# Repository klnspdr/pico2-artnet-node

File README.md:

# pico2-artnet-node

## Upload to JLCPCB
To generate files for uploading to JLCPCB, the plugin ["Fabrication Toolkit"](https://github.com/bennymeg/Fabrication-Toolkit) is used. It generates Gerber and BOM/Pick'n'Places files. Upload the `.zip` in `production/` as the Gerber file and in PCBA upload `bom.csv`  and `positions.csv`

## Estimated Price

PCB + SMD Components: 8.146$ / board
Missing Components:
    - 4x XLR Connectors (~1.40€ / piece)
    - 1x WizNet W5500-EVB-PICO2 (~12€ / piece)
    - 1x B0505S (~1.05$ / piece)
    - 1x WIZPoE Module (~8€ / piece)
    - 2x 1x20 2.54mm Pinsocket THT Vertical (~0.15$ / piece)
    - 3x 1x4 2.54mm Pinsocket THT Vertical (~0.05$ / piece)

=> Overall cost per board (without shipping): ~20€ / ~28€ (without/with PoE)

## Possible other features / TODOs
- [x] LED showing powered state
- [x] Pinheader for I2C
- [x] Levelshifter for WS2812 etc driving (maybe with separate power input?)
- [ ] Test points
- [x] Silkscreen
- [ ] Mounting Holes
- [ ] JLC Ordering Number / mounting holes for PCBA

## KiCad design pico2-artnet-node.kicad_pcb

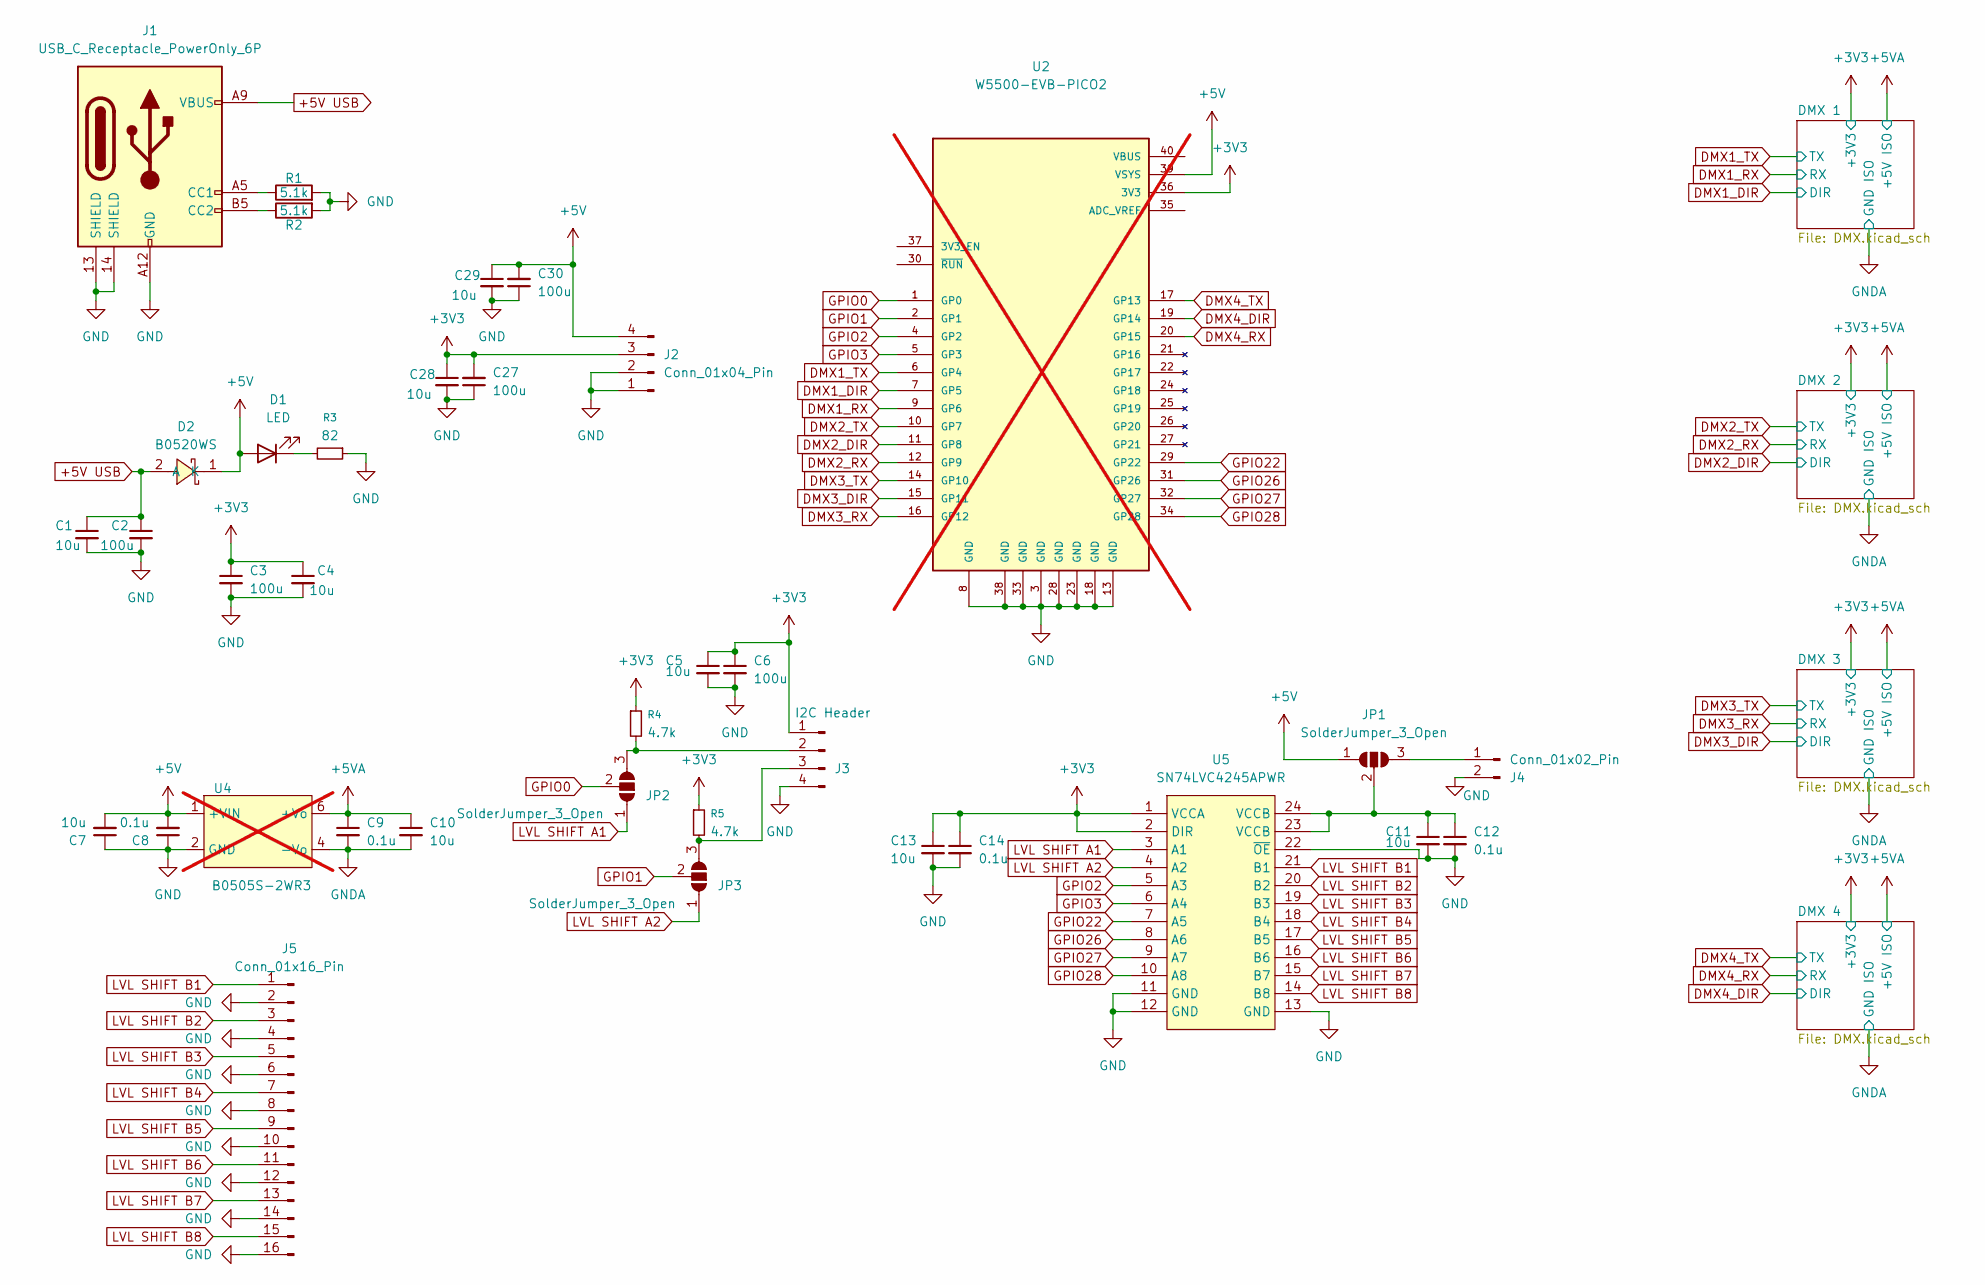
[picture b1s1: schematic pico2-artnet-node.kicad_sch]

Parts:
C1, C4, C5, C7, C10, C11, C13, C28, C29: 10u; C_0603_1608Metric; LCSC Part C19702
C2, C3, C6, C27, C30: 100u; C_1206_3216Metric; LCSC Part C15008
C8, C9, C12, C14: 0.1u; C_0603_1608Metric; LCSC Part C14663
D1: LED; LED_0805_2012Metric; LCSC Part C2297
D2: B0520WS; SOD-323_L1.7-W1.3-LS2.6-RD-1; LCSC Part C7502696
J1: USB_C_Receptacle_PowerOnly_6P; USB-C-SMD_YPE-C-6PWTL-10-0108_Board-overhang; LCSC Part C30167331
J2: Conn_01x04_Pin; FanPinHeader_1x04_P2.54mm_Vertical
J3: I2C Header; FanPinHeader_1x04_P2.54mm_Vertical
J4: Conn_01x02_Pin; PinSocket_1x02_P2.54mm_Vertical
J5: Conn_01x16_Pin; PinSocket_1x16_P2.54mm_Vertical
JP1, JP2, JP3: SolderJumper_3_Open; PinHeader_1x03_P2.54mm_Vertical
R1, R2: 5.1k; R_0603_1608Metric
R3: 82; R_0603_1608Metric
R4, R5: 4.7k; R_0603_1608Metric
U2: W5500-EVB-PICO2; MODULE_W5500-EVB-PICO2; PARTREV 2022-01-28; not fitted
U4: B0505S-2WR3; PWRM-TH_BXXXXS-2WR3; LCSC Part C5369473; not fitted
U5: SN74LVC4245APWR; TSSOP-24_L7.8-W4.4-P0.65-LS6.4-BL; LCSC Part C7859

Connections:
+3V3: C3.1, C4.1, C5.1, C6.1, C13.1, C14.1, C27.2, C28.1, J2.3, J3.1, R4.1, R5.1, U2.36 (3V3), U5.1 (VCCA), U5.2 (DIR); also elsewhere on the board
+5V: C7.2, C8.2, C29.1, C30.2, D1.2 (A), D2.1 (K), J2.4, JP1.1 (A), U2.39 (VSYS), U4.1 (+VIN)
+5V USB: C1.1, C2.1, D2.2 (A), J1.A9 (VBUS), J1.B9 (VBUS)
+5VA: C9.1, C10.1, U4.6 (+Vo); also elsewhere on the board
DMX1_DIR: U2.7 (GP5); also elsewhere on the board
DMX1_RX: U2.9 (GP6); also elsewhere on the board
DMX1_TX: U2.6 (GP4); also elsewhere on the board
DMX2_DIR: U2.11 (GP8); also elsewhere on the board
DMX2_RX: U2.12 (GP9); also elsewhere on the board
DMX2_TX: U2.10 (GP7); also elsewhere on the board
DMX3_DIR: U2.15 (GP11); also elsewhere on the board
DMX3_RX: U2.16 (GP12); also elsewhere on the board
DMX3_TX: U2.14 (GP10); also elsewhere on the board
DMX4_DIR: U2.19 (GP14); also elsewhere on the board
DMX4_RX: U2.20 (GP15); also elsewhere on the board
DMX4_TX: U2.17 (GP13); also elsewhere on the board
GND: C1.2, C2.2, C3.2, C4.2, C5.2, C6.2, C7.1, C8.1, C11.2, C12.2, C13.2, C14.2, C27.1, C28.2, C29.2, C30.1, J1.13 (SHIELD), J1.14 (SHIELD), J1.A12 (GND), J1.B12 (GND), J2.1, J2.2, J3.4, J4.2, J5.2, J5.4, J5.6, J5.8, J5.10, J5.12, J5.14, J5.16, R1.2, R2.2, R3.1, U2.3 (GND), U2.8 (GND), U2.13 (GND), U2.18 (GND), U2.23 (GND), U2.28 (GND), U2.33 (GND), U2.38 (GND), U4.2 (GND), U5.11 (GND), U5.12 (GND), U5.13 (GND), U5.22 (~OE); also elsewhere on the board
GNDA: C9.2, C10.2, U4.4 (-Vo); also elsewhere on the board
GPIO0: JP2.2 (C), U2.1 (GP0)
GPIO1: JP3.2 (C), U2.2 (GP1)
GPIO2: U2.4 (GP2), U5.5 (A3)
GPIO3: U2.5 (GP3), U5.6 (A4)
GPIO22: U2.29 (GP22), U5.7 (A5)
GPIO26: U2.31 (GP26), U5.8 (A6)
GPIO27: U2.32 (GP27), U5.9 (A7)
GPIO28: U2.34 (GP28), U5.10 (A8)
LVL SHIFT A1: JP2.1 (A), U5.3 (A1)
LVL SHIFT A2: JP3.1 (A), U5.4 (A2)
LVL SHIFT B1: J5.1, U5.21 (B1)
LVL SHIFT B2: J5.3, U5.20 (B2)
LVL SHIFT B3: J5.5, U5.19 (B3)
LVL SHIFT B4: J5.7, U5.18 (B4)
LVL SHIFT B5: J5.9, U5.17 (B5)
LVL SHIFT B6: J5.11, U5.16 (B6)
LVL SHIFT B7: J5.13, U5.15 (B7)
LVL SHIFT B8: J5.15, U5.14 (B8)
unnamed: D1.1 (K), R3.2
unnamed: J1.A5 (CC1), R1.1
unnamed: J1.B5 (CC2), R2.1
unnamed: J3.2, JP2.3 (B), R4.2
unnamed: J3.3, JP3.3 (B), R5.2
unnamed: J4.1, JP1.3 (B)
unnamed: C11.1, C12.1, JP1.2 (C), U5.23 (VCCB), U5.24 (VCCB)

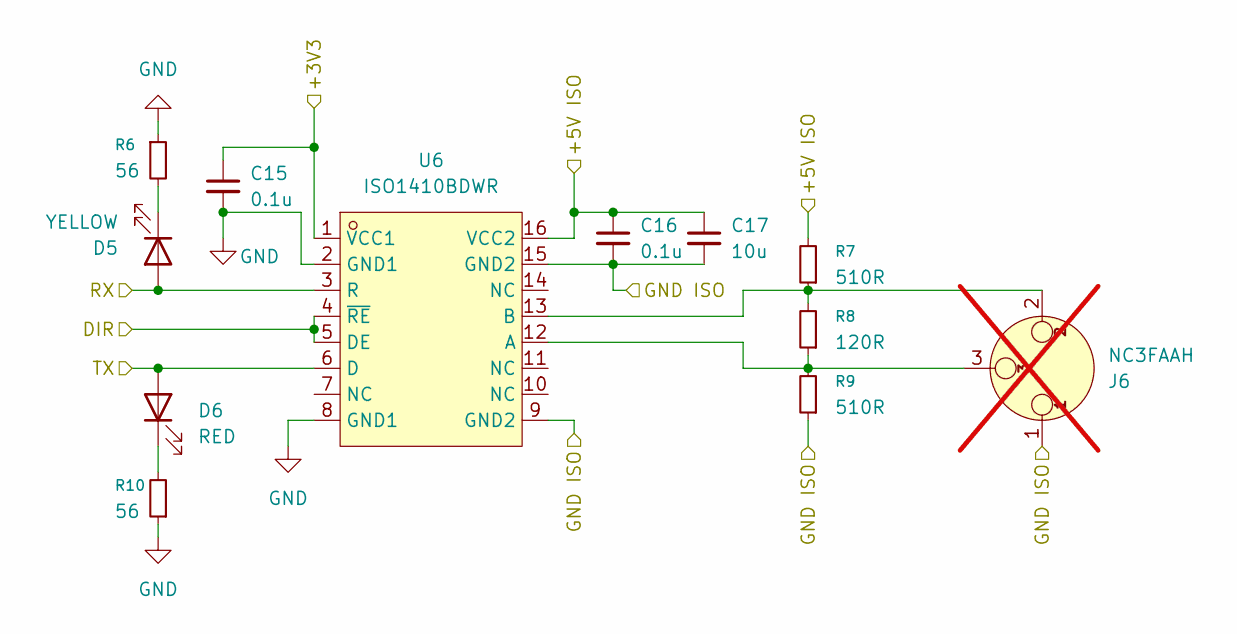
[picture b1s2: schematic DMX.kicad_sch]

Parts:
C15, C16: 0.1u; C_0603_1608Metric; LCSC Part C14663
C17: 10u; C_0603_1608Metric; LCSC Part C19702
D5: YELLOW; LED_0805_2012Metric; LCSC Part C2296
D6: RED; LED_0805_2012Metric; LCSC Part C84256
J6: NC3FAAH; Jack_XLR_Neutrik_NC3FAAH_Horizontal_Board-Overhang; LCSC Part C368521; not fitted
R6, R10: 56; R_0603_1608Metric
R7, R9: 510R; R_0603_1608Metric
R8: 120R; R_0603_1608Metric
U6: ISO1410BDWR; SOIC-16_L10.3-W7.5-P1.27-LS10.3-BL; LCSC Part C2671027

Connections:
+3V3: C15.1, U6.1 (VCC1); also elsewhere on the board
+5VA: C16.1, C17.1, R7.2, U6.16 (VCC2); also elsewhere on the board
DMX1_DIR: U6.4 (~RE), U6.5 (DE); also elsewhere on the board
DMX1_RX: D5.2 (A), U6.3 (R); also elsewhere on the board
DMX1_TX: D6.2 (A), U6.6 (D); also elsewhere on the board
GND: C15.2, R6.1, R10.1, U6.2 (GND1), U6.8 (GND1); also elsewhere on the board
GNDA: C16.2, C17.2, J6.1, R9.1, U6.9 (GND2), U6.15 (GND2); also elsewhere on the board
unnamed: D5.1 (K), R6.2
unnamed: D6.1 (K), R10.2
unnamed: J6.3, R8.1, R9.2, U6.12 (A)
unnamed: J6.2, R7.1, R8.2, U6.13 (B)

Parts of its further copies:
C18, C19, C21, C22, C24, C25: 0.1u; C_0603_1608Metric; LCSC Part C14663
C20, C23, C26: 10u; C_0603_1608Metric; LCSC Part C19702
D7, D9, D11: YELLOW; LED_0805_2012Metric; LCSC Part C2296
D8, D10, D12: RED; LED_0805_2012Metric; LCSC Part C84256
J7, J8, J9: NC3FAAH; Jack_XLR_Neutrik_NC3FAAH_Horizontal_Board-Overhang; LCSC Part C368521; not fitted
R11, R15, R16, R20, R21, R25: 56; R_0603_1608Metric
R12, R14, R17, R19, R22, R24: 510R; R_0603_1608Metric
R13, R18, R23: 120R; R_0603_1608Metric
U7, U8, U9: ISO1410BDWR; SOIC-16_L10.3-W7.5-P1.27-LS10.3-BL; LCSC Part C2671027

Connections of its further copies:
+3V3: C18.1, C21.1, C24.1, U7.1 (VCC1), U8.1 (VCC1), U9.1 (VCC1); also elsewhere on the board
+5VA: C19.1, C20.1, C22.1, C23.1, C25.1, C26.1, R12.2, R17.2, R22.2, U7.16 (VCC2), U8.16 (VCC2), U9.16 (VCC2); also elsewhere on the board
DMX2_DIR: U7.4 (~RE), U7.5 (DE); also elsewhere on the board
DMX2_RX: D7.2 (A), U7.3 (R); also elsewhere on the board
DMX2_TX: D8.2 (A), U7.6 (D); also elsewhere on the board
DMX3_DIR: U8.4 (~RE), U8.5 (DE); also elsewhere on the board
DMX3_RX: D9.2 (A), U8.3 (R); also elsewhere on the board
DMX3_TX: D10.2 (A), U8.6 (D); also elsewhere on the board
DMX4_DIR: U9.4 (~RE), U9.5 (DE); also elsewhere on the board
DMX4_RX: D11.2 (A), U9.3 (R); also elsewhere on the board
DMX4_TX: D12.2 (A), U9.6 (D); also elsewhere on the board
GND: C18.2, C21.2, C24.2, R11.1, R15.1, R16.1, R20.1, R21.1, R25.1, U7.2 (GND1), U7.8 (GND1), U8.2 (GND1), U8.8 (GND1), U9.2 (GND1), U9.8 (GND1); also elsewhere on the board
GNDA: C19.2, C20.2, C22.2, C23.2, C25.2, C26.2, J7.1, J8.1, J9.1, R14.1, R19.1, R24.1, U7.9 (GND2), U7.15 (GND2), U8.9 (GND2), U8.15 (GND2), U9.9 (GND2), U9.15 (GND2); also elsewhere on the board
unnamed: D7.1 (K), R11.2
unnamed: D8.1 (K), R15.2
unnamed: D9.1 (K), R16.2
unnamed: D10.1 (K), R20.2
unnamed: D11.1 (K), R21.2
unnamed: D12.1 (K), R25.2
unnamed: J7.3, R13.1, R14.2, U7.12 (A)
unnamed: J7.2, R12.1, R13.2, U7.13 (B)
unnamed: J8.3, R18.1, R19.2, U8.12 (A)
unnamed: J8.2, R17.1, R18.2, U8.13 (B)
unnamed: J9.3, R23.1, R24.2, U9.12 (A)
unnamed: J9.2, R22.1, R23.2, U9.13 (B)

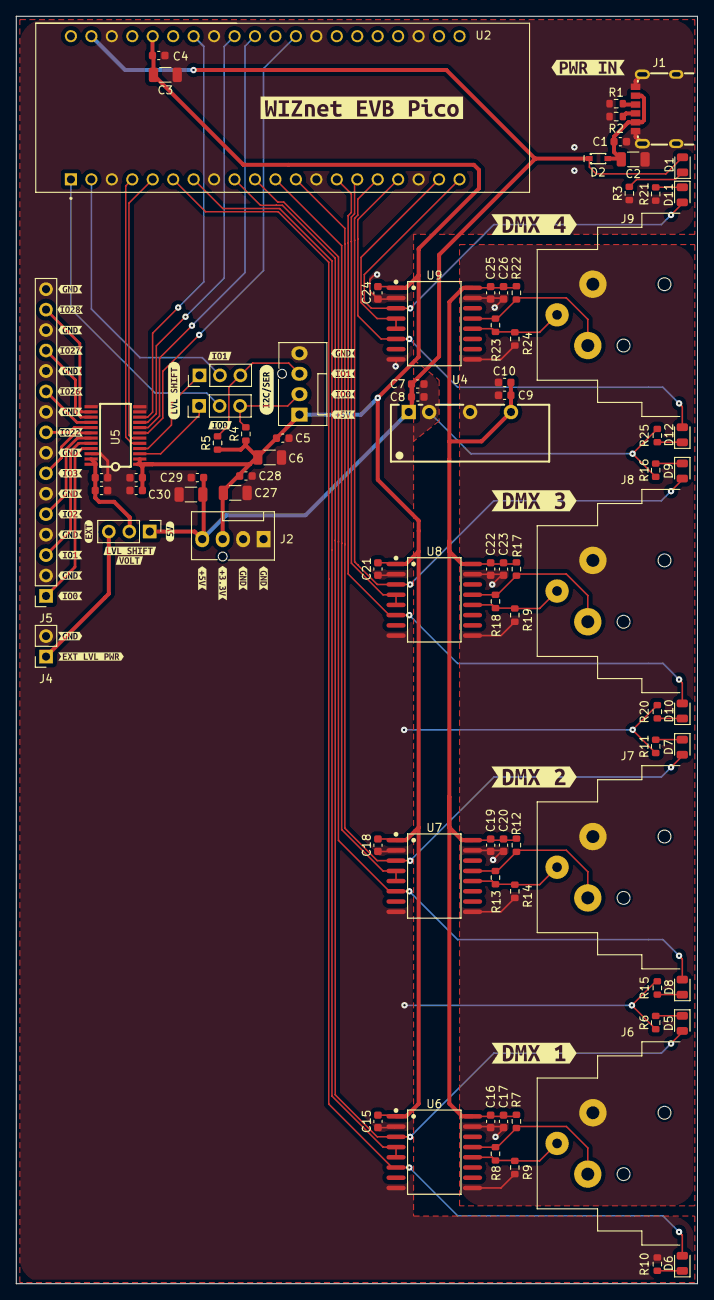
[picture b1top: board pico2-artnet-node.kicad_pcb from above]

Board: 2 copper layers, 84.6 x 157.4 mm, 124 parts (0 on the bottom side), 59 nets.

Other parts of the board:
kibuzzard-68DD1E8E: G***; kibuzzard-68DD1E8E
kibuzzard-68DD1E9C: G***; kibuzzard-68DD1E9C
kibuzzard-68DD1EFE: G***; kibuzzard-68DD1EFE
kibuzzard-68DD1F08: G***; kibuzzard-68DD1F08
kibuzzard-68DD1F80: G***; kibuzzard-68DD1F80
kibuzzard-68DD3F78: G***; kibuzzard-68DD3F78
kibuzzard-68DD21E1, kibuzzard-68DD21E1#2, kibuzzard-68DD21E1#3, kibuzzard-68DD21E1#4, kibuzzard-68DD21E1#5, kibuzzard-68DD21E1#6, kibuzzard-68DD21E1#7, kibuzzard-68DD21E1#8: G***; kibuzzard-68DD21E1
kibuzzard-68DD22C2: G***; kibuzzard-68DD22C2
kibuzzard-68DD22D5: G***; kibuzzard-68DD22D5
kibuzzard-68DD22E0: G***; kibuzzard-68DD22E0
kibuzzard-68DD22E9: G***; kibuzzard-68DD22E9
kibuzzard-68DD22F0: G***; kibuzzard-68DD22F0
kibuzzard-68DD23A7: G***; kibuzzard-68DD23A7
kibuzzard-68DD23B6: G***; kibuzzard-68DD23B6
kibuzzard-68DD28CA: G***; kibuzzard-68DD28CA
kibuzzard-68DD43ED, kibuzzard-68DD43ED#2: G***; kibuzzard-68DD43ED
kibuzzard-68DD227C: G***; kibuzzard-68DD227C
kibuzzard-68DD228E: G***; kibuzzard-68DD228E
kibuzzard-68DD244B: G***; kibuzzard-68DD244B
kibuzzard-68DD245B: G***; kibuzzard-68DD245B
kibuzzard-68DD444E: G***; kibuzzard-68DD444E
kibuzzard-68DD501A: G***; kibuzzard-68DD501A
kibuzzard-68DD2296: G***; kibuzzard-68DD2296
kibuzzard-68DD2361: G***; kibuzzard-68DD2361
kibuzzard-68DD2414: G***; kibuzzard-68DD2414
kibuzzard-68DD2461: G***; kibuzzard-68DD2461
kibuzzard-68DD2906: G***; kibuzzard-68DD2906
kibuzzard-68DD2926: G***; kibuzzard-68DD2926
kibuzzard-68DD4448: G***; kibuzzard-68DD4448
kibuzzard-68DD4454, kibuzzard-68DD4454#2: G***; kibuzzard-68DD4454
kibuzzard-68DD5009: G***; kibuzzard-68DD5009

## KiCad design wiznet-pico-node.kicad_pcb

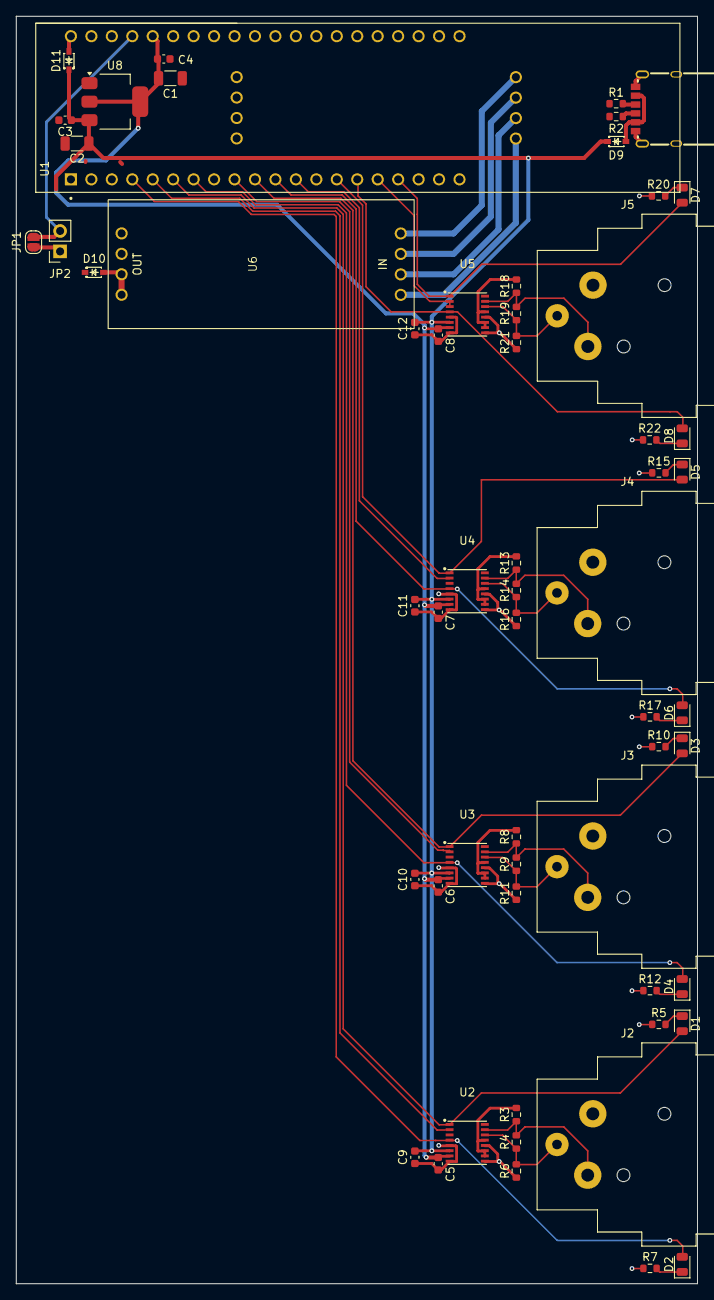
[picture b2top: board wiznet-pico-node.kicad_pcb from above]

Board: 2 copper layers, 84.6 x 157.4 mm, 59 parts (0 on the bottom side), 43 nets.

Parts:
C1, C2: 100u; C_1206_3216Metric
C3, C4, C5, C6, C7, C8, C9, C10, C11, C12: 10u; C_0603_1608Metric
D1, D3, D5, D7: YELLOW; LED_0805_2012Metric
D2, D4, D6, D8: RED; LED_0805_2012Metric
D9, D10, D11: B0520WS; SOD-323_L1.7-W1.3-LS2.6-RD-1
J2, J3, J4, J5: NC3FAAH; Jack_XLR_Neutrik_NC3FAAH_Horizontal
J6: USB_C_Receptacle_PowerOnly_6P; USB-C-SMD_YPE-C-6PWTL-10-0108
JP1: disable onboard LDO; SolderJumper-2_P1.3mm_Open_RoundedPad1.0x1.5mm
JP2: disable onboard LDO; PinSocket_1x02_P2.54mm_Vertical
R1, R2: 5.1k; R_0603_1608Metric
R3, R6, R8, R11, R13, R16, R18, R21: 510R; R_0603_1608Metric
R4, R9, R14, R19: 120R; R_0603_1608Metric
R5, R10, R15, R20: 75R; R_0603_1608Metric
R7, R12, R17, R22: 51R; R_0603_1608Metric
U1: W5500-EVB-PICO2; MODULE_W5500-EVB-PICO2
U2, U3, U4, U5: CA-IS2092A; LGA-16_L5.2-W4.7-P0.65-TL_CA-IS2062A-FRANK2
U6: WIZPoE Hat
U8: AMS1117-3.3; SOT-223-3_TabPin2

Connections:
+3V3: C1.1, C4.1, C5.1, C6.1, C7.1, C8.1, U1.36 (3V3), U2.7 (VDDL), U3.7 (VDDL), U4.7 (VDDL), U5.7 (VDDL), U8.2 (VO)
+5V: C2.1, C3.1, C9.1, C10.1, C11.1, C12.1, D9.1 (K), D10.1 (K), D11.1 (K), U2.6 (VDDP), U3.6 (VDDP), U4.6 (VDDP), U5.6 (VDDP), U8.3 (VI)
+5V PoE: D10.2 (A), U6.1 (5V)
+5V RP: D11.2 (A), U1.40 (VBUS)
+5V USB: D9.2 (A), J6.A9 (VBUS), J6.B9 (VBUS)
+5VA: R3.2, R8.2, R13.2, R18.2, U2.10 (VISOIN), U2.11 (VISOOUT), U2.13 (SEL), U3.10 (VISOIN), U3.11 (VISOOUT), U3.13 (SEL), U4.10 (VISOIN), U4.11 (VISOOUT), U4.13 (SEL), U5.10 (VISOIN), U5.11 (VISOOUT), U5.13 (SEL)
AGND: J2.1, J3.1, J4.1, J5.1, R6.1, R11.1, R16.1, R21.1, U2.9 (GND2), U2.12 (GND2), U3.9 (GND2), U3.12 (GND2), U4.9 (GND2), U4.12 (GND2), U5.9 (GND2), U5.12 (GND2)
DMX1_DIR: U1.5 (GP3), U2.2 (~RE), U2.3 (DE)
DMX1_RX: D1.2 (A), U1.6 (GP4), U2.1 (RO)
DMX1_TX: D2.2 (A), U1.4 (GP2), U2.4 (DI)
DMX2_DIR: U1.9 (GP6), U3.2 (~RE), U3.3 (DE)
DMX2_RX: D3.2 (A), U1.10 (GP7), U3.1 (RO)
DMX2_TX: D4.2 (A), U1.7 (GP5), U3.4 (DI)
DMX3_DIR: U1.12 (GP9), U4.2 (~RE), U4.3 (DE)
DMX3_RX: D5.2 (A), U1.14 (GP10), U4.1 (RO)
DMX3_TX: D6.2 (A), U1.11 (GP8), U4.4 (DI)
DMX4_DIR: U1.16 (GP12), U5.2 (~RE), U5.3 (DE)
DMX4_RX: D7.2 (A), U1.17 (GP13), U5.1 (RO)
DMX4_TX: D8.2 (A), U1.15 (GP11), U5.4 (DI)
GND: C1.2, C2.2, C3.2, C4.2, C5.2, C6.2, C7.2, C8.2, C9.2, C10.2, C11.2, C12.2, J6.13 (SHIELD), J6.14 (SHIELD), J6.A12 (GND), J6.B12 (GND), JP1.1 (A), JP2.1 (A), R1.2, R2.2, R5.1, R7.1, R10.1, R12.1, R15.1, R17.1, R20.1, R22.1, U1.3 (GND), U1.8 (GND), U1.13 (GND), U1.18 (GND), U1.23 (GND), U1.28 (GND), U1.33 (GND), U1.38 (GND), U1.42 (GND), U2.5 (GND1), U2.8 (GND1), U3.5 (GND1), U3.8 (GND1), U4.5 (GND1), U4.8 (GND1), U5.5 (GND1), U5.8 (GND1), U6.2 (GND), U8.1 (GND)
unnamed: D1.1 (K), R5.2
unnamed: D2.1 (K), R7.2
unnamed: D3.1 (K), R10.2
unnamed: D4.1 (K), R12.2
unnamed: D5.1 (K), R15.2
unnamed: D6.1 (K), R17.2
unnamed: D7.1 (K), R20.2
unnamed: D8.1 (K), R22.2
unnamed: J6.A5 (CC1), R1.1
unnamed: J6.B5 (CC2), R2.1
unnamed: JP1.2 (B), JP2.2 (B), U1.37 (3V3_EN)
unnamed: U1.43 (VC1+), U6.3 (VC1+)
unnamed: U1.44 (VC1-), U6.4 (VC1-)
unnamed: U1.45 (VC2+), U6.5 (VC2+)
unnamed: U1.46 (VC2-), U6.6 (VC2-)
unnamed: J2.3, R4.1, R6.2, U2.14 (A)
unnamed: J2.2, R3.1, R4.2, U2.15 (B)
unnamed: J3.3, R9.1, R11.2, U3.14 (A)
unnamed: J3.2, R8.1, R9.2, U3.15 (B)
unnamed: J4.3, R14.1, R16.2, U4.14 (A)
unnamed: J4.2, R13.1, R14.2, U4.15 (B)
unnamed: J5.3, R19.1, R21.2, U5.14 (A)
unnamed: J5.2, R18.1, R19.2, U5.15 (B)

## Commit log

2025-09-30 add gitignore
2025-09-30 first version, needs changes in DMX circuit
2025-09-30 add production files
2025-09-30 add readme
2025-09-30 rename files
2025-10-01 v0.2 new DMX circuitry
2025-10-01 add ideas/todos
2025-10-01 add levelshifter and silkscreen
2025-10-01 change solder jumpers to pins & power break out
2025-10-01 remove PoE Breakout & rund DRC
